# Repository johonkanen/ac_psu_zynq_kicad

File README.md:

# zynq_soc_board

Linux-capable control card for the AC in/out lab power supply, based on an AMD **Zynq-7000 (XC7Z020-CLG484)**. It
has 1 GB DDR3L (2 × x16), Gigabit Ethernet (RTL8211F) and eMMC. It plugs into the power supply baseboard
([ac_psu_kicad](https://github.com/johonkanen/ac_psu_kicad)) in the place of the Ti60F225, Agilex 5
([agilex3_soc_control_card](https://github.com/johonkanen/agilex3_soc_control_card)) and Ti135
([efinix_soc_board](https://github.com/johonkanen/efinix_soc_board)) cards.

The SoC, the DDR3 and their routing are not laid out here. They are reused, as a routed block, from the open-source
[juliancoy/zynqPCB](https://github.com/juliancoy/zynqPCB) (MIT); see **[PLAN.md](PLAN.md)** and `NOTICE`. Licence: MIT.

| | |
|---|---|
| [STATUS.md](STATUS.md) | **start here:** status, decisions, next steps, how to run the tools |
| [PLAN.md](PLAN.md) | plan, source survey and decisions |
| [DDR3_REVIEW.md](DDR3_REVIEW.md) | UG933 review of the candidate DDR3 blocks |
| [POWER_BUDGET.md](POWER_BUDGET.md) | rail currents (Vivado `report_power`), regulators, thermal |
| [ZYNQ_PCB_NOTES.md](ZYNQ_PCB_NOTES.md) | Zynq-7000 rules: supplies, sequencing, boot straps, MIO, configuration pins, DDR3 routing |
| `tools/ddr3_review.py` | die-to-die DDR delay and topology check (KiCad Python) |
| `tools/zsolve_cases.py` | impedance and propagation speed for the stack-up (uses `tools/zsolve.py`) |
| `tools/stackup_scan.py` | impedance of one trace width on every layer of the JLC 8-layer templates |
| [REUSE_LOG.md](REUSE_LOG.md) | every change to the reused DDR3 block |
| `vivado/pinplan/` | Vivado pin plan: `pinplan.py` builds and checks the PS7 + PL pins; results in `zynq_pinplan.csv`, `ps7_mio.csv`, `mio.csv` |

Set-up after cloning:

```
git submodule update --init   # tools/jlc (jlc-tools), tools/p2k (proteus2kicad, KiCad 10 env), reference/zynqpcb (DDR3 source)
```

KiCad 10 runs through `tools/p2k/bin/kicad_env.sh` (AppImage at `~/kicad/kicad-10.0.7-x86_64.AppImage`). Vivado 2024.2
runs the pin plan (`vivado/pinplan/pinplan.py`).

Status: phase 3, placement (schematic done, DDR3 block imported, parts placed); next: routing. See
[STATUS.md](STATUS.md).

## Board

<!-- board-plots:start -->
<!-- Generated by kicad-board-plots; edits between these markers are overwritten. -->

3D renders and copper layers of `kicad/zynq_card.kicad_pcb`, the layers in stack order without silkscreen. Plotted by [kicad-board-plots](https://github.com/johonkanen/kicad-board-plots) on each board change; the images live on the `renders` branch.

<table>
<tr>
<td align="center"><br><b>3D, top</b></td>
<td align="center"><br><b>3D, bottom (seen from below)</b></td>
</tr>
<tr>
<td align="center"><br><b>F.Cu: signal, GND, 1V35 pours (top)</b></td>
<td align="center"><br><b>In1.Cu: GND plane</b></td>
</tr>
<tr>
<td align="center"><br><b>In2.Cu: signal, 1V8 pour</b></td>
<td align="center"><br><b>In3.Cu: GND plane</b></td>
</tr>
<tr>
<td align="center"><br><b>In4.Cu: signal, VCCAUX, 1V8 pours</b></td>
<td align="center"><br><b>In5.Cu: GND plane</b></td>
</tr>
<tr>
<td align="center"><br><b>In6.Cu: signal, VCCAUX, 3V3, 1V0 pours</b></td>
<td align="center"><br><b>B.Cu: signal, 1V8, 1V35, DDR3_VTT, 3V3, 5V0 and 2 more pours (bottom, seen from the top)</b></td>
</tr>
</table>

<!-- board-plots:end -->

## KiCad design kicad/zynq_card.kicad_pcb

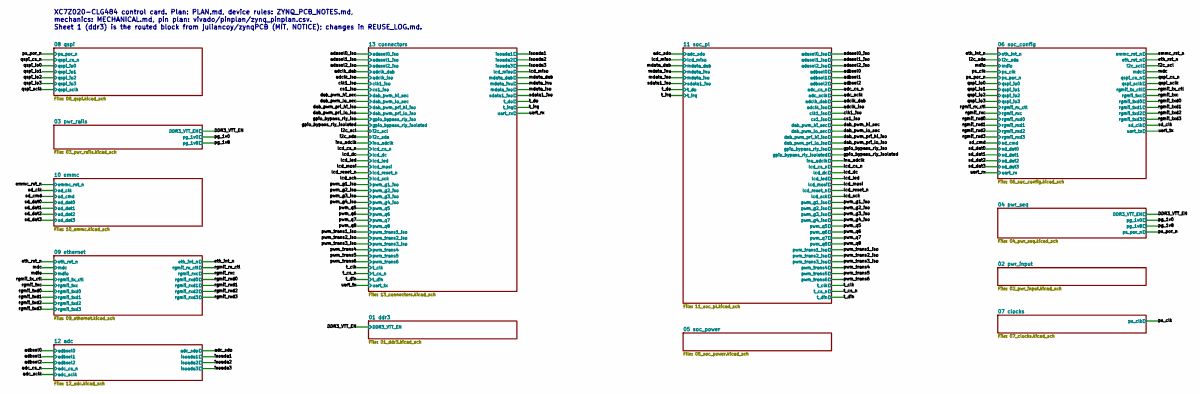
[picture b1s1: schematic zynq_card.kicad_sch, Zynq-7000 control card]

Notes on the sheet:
XC7Z020-CLG484 control card. Plan: PLAN.md, device rules: ZYNQ_PCB_NOTES.md, mechanics: MECHANICAL.md, pin plan: vivado/pinplan/zynq_pinplan.csv. Sheet 1 (ddr3) is the routed block from juliancoy/zynqPCB (MIT, NOTICE); changes in REUSE_LOG.md.

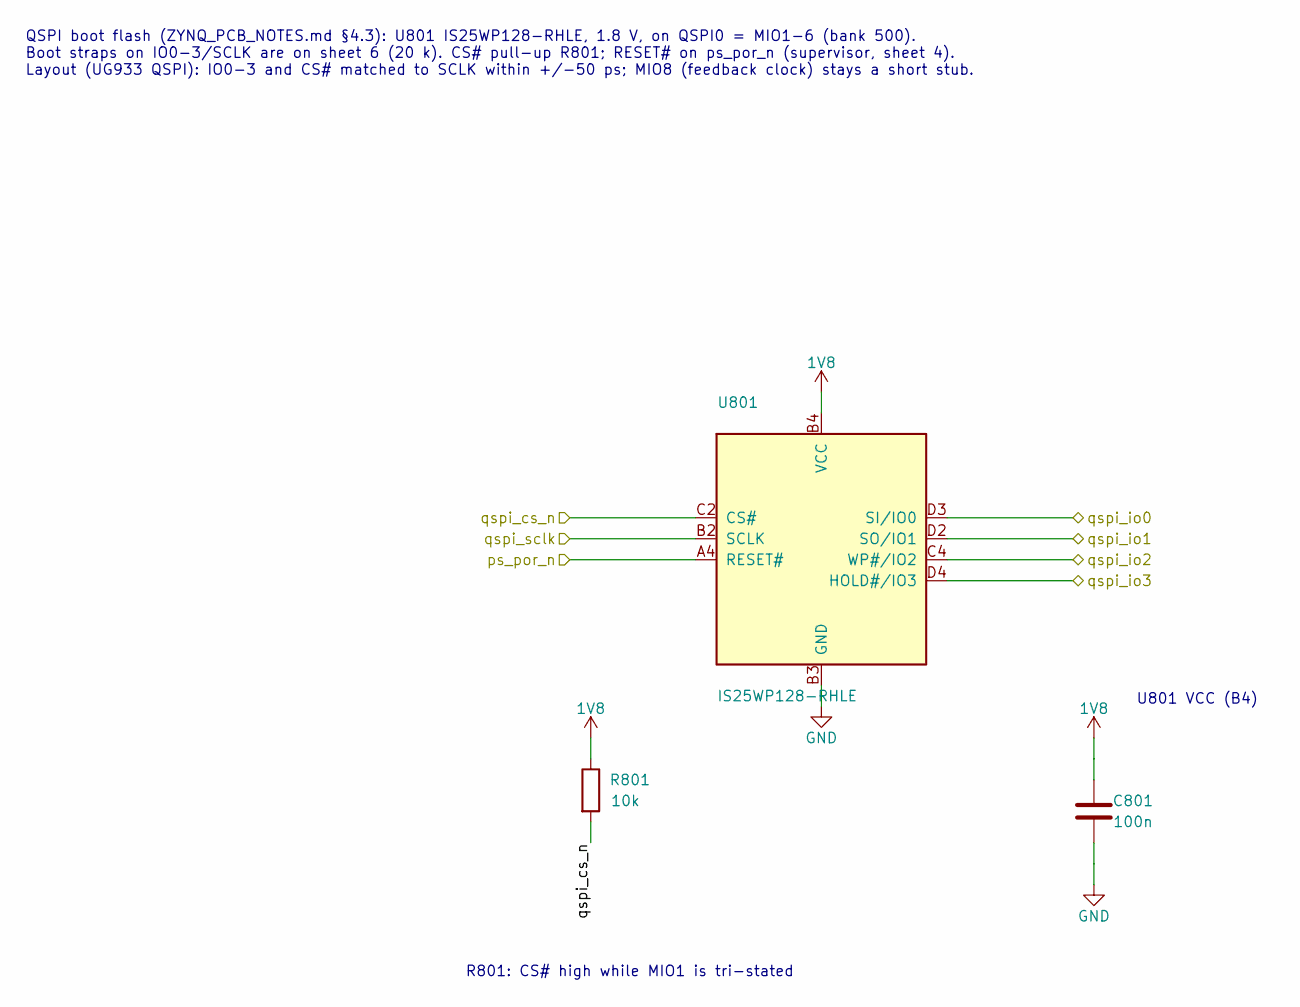
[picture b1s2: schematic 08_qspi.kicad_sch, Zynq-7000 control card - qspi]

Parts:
C801: 100n; C_0402_1005Metric; LCSC C1525
R801: 10k; R_0402_1005Metric; LCSC C25744
U801: IS25WP128-RHLE; MX25U25645G_CSP24_6x8mm_P1.0mm; LCSC C1349419

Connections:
1V8: C801.1, R801.1, U801.B4 (VCC); also elsewhere on the board
/ps_por_n: U801.A4 (RESET#); also elsewhere on the board
/qspi_cs_n: R801.2, U801.C2 (CS#); also elsewhere on the board
/qspi_io0: U801.D3 (SI/IO0); also elsewhere on the board
/qspi_io1: U801.D2 (SO/IO1); also elsewhere on the board
/qspi_io2: U801.C4 (WP#/IO2); also elsewhere on the board
/qspi_io3: U801.D4 (HOLD#/IO3); also elsewhere on the board
/qspi_sclk: U801.B2 (SCLK); also elsewhere on the board
GND: C801.2, U801.B3 (GND); also elsewhere on the board

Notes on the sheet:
QSPI boot flash (ZYNQ_PCB_NOTES.md §4.3): U801 IS25WP128-RHLE, 1.8 V, on QSPI0 = MIO1-6 (bank 500). Boot straps on IO0-3/SCLK are on sheet 6 (20 k). CS# pull-up R801; RESET# on ps_por_n (supervisor, sheet 4). Layout (UG933 QSPI): IO0-3 and CS# matched to SCLK within +/-50 ps; MIO8 (feedback clock) 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
R801: CS# high while MIO1 is tri-stated
U801 VCC (B4)

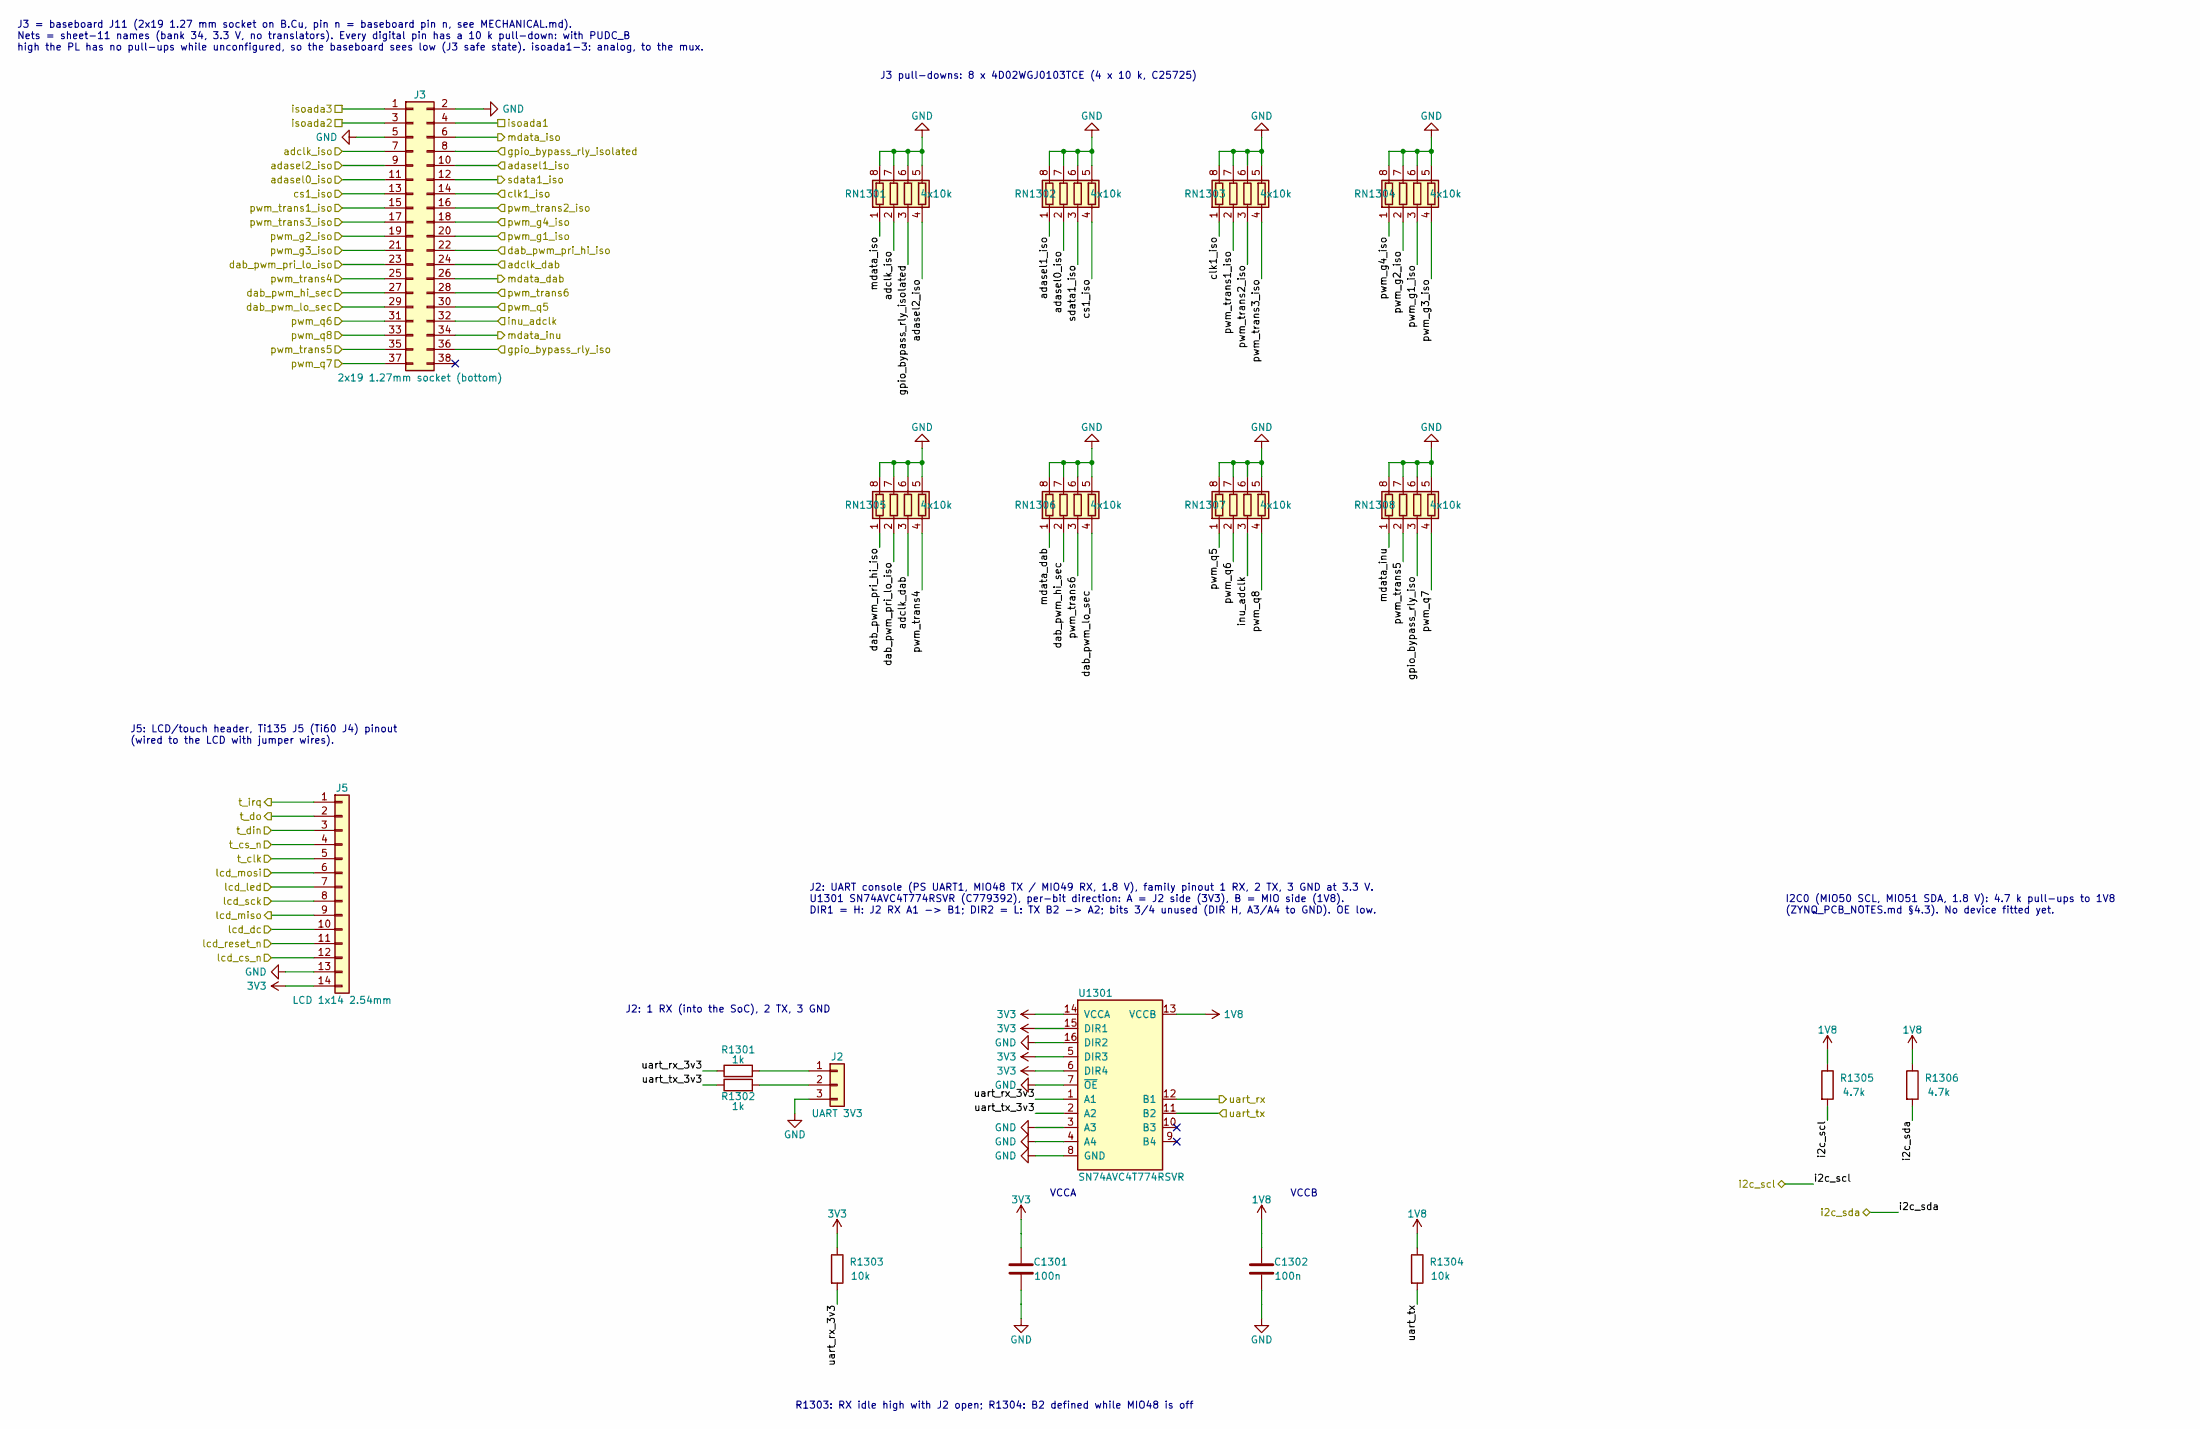
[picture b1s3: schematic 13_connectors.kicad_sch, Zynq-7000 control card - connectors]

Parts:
C1301, C1302: 100n; C_0402_1005Metric; LCSC C1525
J2: UART 3V3; PinHeader_1x03_P2.54mm_Vertical
J3: 2x19 1.27mm socket (bottom); PinSocket_2x19_P1.27mm_Vertical
J5: LCD 1x14 2.54mm; PinHeader_1x14_P2.54mm_Vertical
R1301, R1302: 1k; R_0402_1005Metric; LCSC C11702
R1303, R1304: 10k; R_0402_1005Metric; LCSC C25744
R1305, R1306: 4.7k; R_0402_1005Metric; LCSC C25900
RN1301, RN1302, RN1303, RN1304, RN1305, RN1306, RN1307, RN1308: 4x10k; R_Array_Convex_4x0402; MPN 4D02WGJ0103TCE; LCSC C25725
U1301: SN74AVC4T774RSVR; UQFN-16_1.8x2.6mm_P0.4mm; MPN SN74AVC4T774RSVR; LCSC C779392

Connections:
1V8: C1302.1, R1304.1, R1305.1, R1306.1, U1301.13 (VCCB); also elsewhere on the board
3V3: C1301.1, J5.14, R1303.1, U1301.5 (DIR3), U1301.6 (DIR4), U1301.14 (VCCA), U1301.15 (DIR1); also elsewhere on the board
/13 connectors/uart_rx_3v3: R1301.1, R1303.2, U1301.1 (A1)
/13 connectors/uart_tx_3v3: R1302.1, U1301.2 (A2)
/adasel0_iso: J3.11, RN1302.2 (R2.1); also elsewhere on the board
/adasel1_iso: J3.10, RN1302.1 (R1.1); also elsewhere on the board
/adasel2_iso: J3.9, RN1301.4 (R4.1); also elsewhere on the board
/adclk_dab: J3.24, RN1305.3 (R3.1); also elsewhere on the board
/adclk_iso: J3.7, RN1301.2 (R2.1); also elsewhere on the board
/clk1_iso: J3.14, RN1303.1 (R1.1); also elsewhere on the board
/cs1_iso: J3.13, RN1302.4 (R4.1); also elsewhere on the board
/dab_pwm_hi_sec: J3.27, RN1306.2 (R2.1); also elsewhere on the board
/dab_pwm_lo_sec: J3.29, RN1306.4 (R4.1); also elsewhere on the board
/dab_pwm_pri_hi_iso: J3.22, RN1305.1 (R1.1); also elsewhere on the board
/dab_pwm_pri_lo_iso: J3.23, RN1305.2 (R2.1); also elsewhere on the board
/gpio_bypass_rly_iso: J3.36, RN1308.3 (R3.1); also elsewhere on the board
/gpio_bypass_rly_isolated: J3.8, RN1301.3 (R3.1); also elsewhere on the board
/i2c_scl: R1305.2; also elsewhere on the board
/i2c_sda: R1306.2; also elsewhere on the board
/inu_adclk: J3.32, RN1307.3 (R3.1); also elsewhere on the board
/isoada1: J3.4; also elsewhere on the board
/isoada2: J3.3; also elsewhere on the board
/isoada3: J3.1; also elsewhere on the board
/lcd_cs_n: J5.12; also elsewhere on the board
/lcd_dc: J5.10; also elsewhere on the board
/lcd_led: J5.7; also elsewhere on the board
/lcd_miso: J5.9; also elsewhere on the board
/lcd_mosi: J5.6; also elsewhere on the board
/lcd_reset_n: J5.11; also elsewhere on the board
/lcd_sck: J5.8; also elsewhere on the board
/mdata_dab: J3.26, RN1306.1 (R1.1); also elsewhere on the board
/mdata_inu: J3.34, RN1308.1 (R1.1); also elsewhere on the board
/mdata_iso: J3.6, RN1301.1 (R1.1); also elsewhere on the board
/pwm_g1_iso: J3.20, RN1304.3 (R3.1); also elsewhere on the board
/pwm_g2_iso: J3.19, RN1304.2 (R2.1); also elsewhere on the board
/pwm_g3_iso: J3.21, RN1304.4 (R4.1); also elsewhere on the board
/pwm_g4_iso: J3.18, RN1304.1 (R1.1); also elsewhere on the board
/pwm_q5: J3.30, RN1307.1 (R1.1); also elsewhere on the board
/pwm_q6: J3.31, RN1307.2 (R2.1); also elsewhere on the board
/pwm_q7: J3.37, RN1308.4 (R4.1); also elsewhere on the board
/pwm_q8: J3.33, RN1307.4 (R4.1); also elsewhere on the board
/pwm_trans1_iso: J3.15, RN1303.2 (R2.1); also elsewhere on the board
/pwm_trans2_iso: J3.16, RN1303.3 (R3.1); also elsewhere on the board
/pwm_trans3_iso: J3.17, RN1303.4 (R4.1); also elsewhere on the board
/pwm_trans4: J3.25, RN1305.4 (R4.1); also elsewhere on the board
/pwm_trans5: J3.35, RN1308.2 (R2.1); also elsewhere on the board
/pwm_trans6: J3.28, RN1306.3 (R3.1); also elsewhere on the board
/sdata1_iso: J3.12, RN1302.3 (R3.1); also elsewhere on the board
/t_clk: J5.5; also elsewhere on the board
/t_cs_n: J5.4; also elsewhere on the board
/t_din: J5.3; also elsewhere on the board
/t_do: J5.2; also elsewhere on the board
/t_irq: J5.1; also elsewhere on the board
/uart_rx: U1301.12 (B1); also elsewhere on the board
/uart_tx: R1304.2, U1301.11 (B2); also elsewhere on the board
GND: C1301.2, C1302.2, J2.3, J3.2, J3.5, J5.13, RN1301.5 (R4.2), RN1301.6 (R3.2), RN1301.7 (R2.2), RN1301.8 (R1.2), RN1302.5 (R4.2), RN1302.6 (R3.2), RN1302.7 (R2.2), RN1302.8 (R1.2), RN1303.5 (R4.2), RN1303.6 (R3.2), RN1303.7 (R2.2), RN1303.8 (R1.2), RN1304.5 (R4.2), RN1304.6 (R3.2), RN1304.7 (R2.2), RN1304.8 (R1.2), RN1305.5 (R4.2), RN1305.6 (R3.2), RN1305.7 (R2.2), RN1305.8 (R1.2), RN1306.5 (R4.2), RN1306.6 (R3.2), RN1306.7 (R2.2), RN1306.8 (R1.2), RN1307.5 (R4.2), RN1307.6 (R3.2), RN1307.7 (R2.2), RN1307.8 (R1.2), RN1308.5 (R4.2), RN1308.6 (R3.2), RN1308.7 (R2.2), RN1308.8 (R1.2), U1301.3 (A3), U1301.4 (A4), U1301.7 (~OE), U1301.8 (GND), U1301.16 (DIR2); also elsewhere on the board
unnamed: J2.1, R1301.2
unnamed: J2.2, R1302.2

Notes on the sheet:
J3 = baseboard J11 (2x19 1.27 mm socket on B.Cu, pin n = baseboard pin n, see MECHANICAL.md). Nets = sheet-11 names (bank 34, 3.3 V, no translators). Every digital pin has a 10 k pull-down: with PUDC_B high the PL has no pull-ups while unconfigured, so the baseboard sees low (J3 safe state). isoada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
J3 pull-downs: 8 x 4D02WGJ0103TCE (4 x 10 k, C25725)
J5: LCD/touch header, Ti135 J5 (Ti60 J4) pinout (wired to the LCD with jumper wires).
J2: UART console (PS UART1, MIO48 TX / MIO49 RX, 1.8 V), family pinout 1 RX, 2 TX, 3 GND at 3.3 V. U1301 SN74AVC4T774RSVR (C779392), per-bit direction: A = J2 side (3V3), B = MIO side (1V8). DIR1 = H: J2 RX A1 -> B1; DIR2 = L: TX B2 -> A2; bits 3/4 unused (DIR H, A3/A4 to GND). OE low.
VCCA
VCCB
J2: 1 RX (into the SoC), 2 TX, 3 GND
R1303: RX idle high with J2 open; R1304: B2 defined while MIO48 is off
I2C0 (MIO50 SCL, MIO51 SDA, 1.8 V): 4.7 k pull-ups to 1V8 (ZYNQ_PCB_NOTES.md §4.3). No device fitted yet.

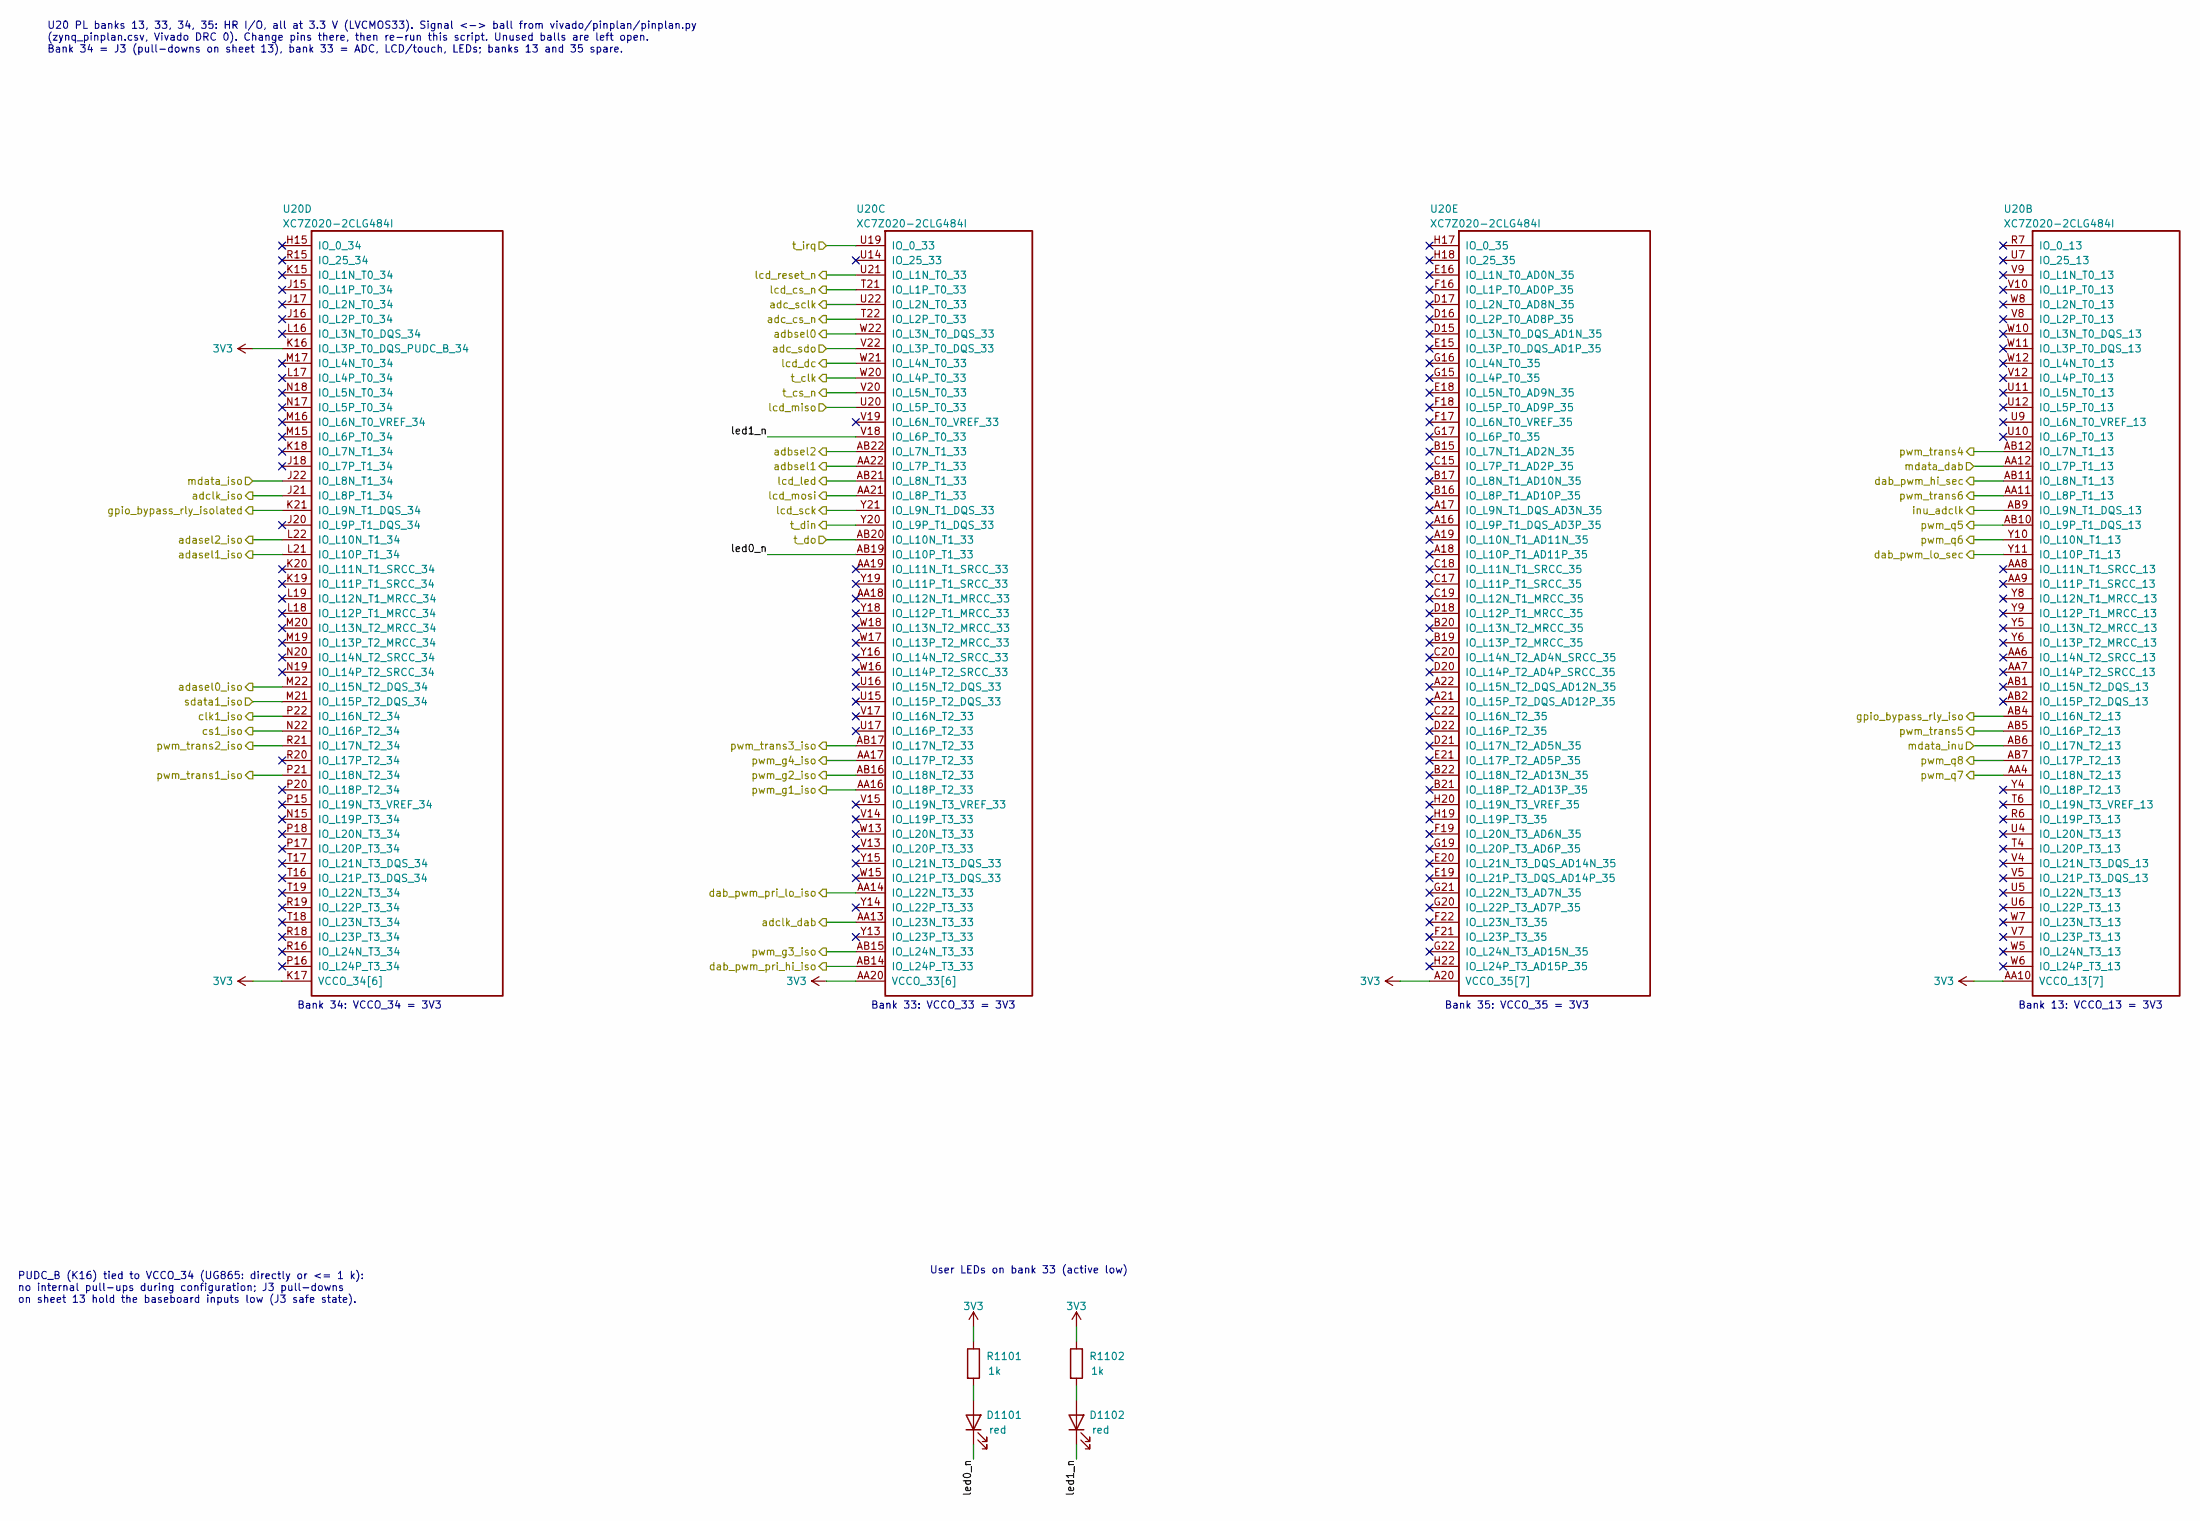
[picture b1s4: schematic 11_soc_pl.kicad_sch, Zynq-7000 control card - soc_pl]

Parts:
D1101, D1102: red; LED_0603_1608Metric; MPN KT-0603R; LCSC C2286
R1101, R1102: 1k; R_0402_1005Metric; LCSC C11702
U20: XC7Z020-2CLG484I; BGA-484_19.0x19.0mm_Layout22x22_P0.80mm_dia0.40mm; MPN XC7Z020-2CLG484I; LCSC C157624

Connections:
3V3: R1101.1, R1102.1, U20.A20 (VCCO_35[7]), U20.AA10 (VCCO_13[7]), U20.AA20 (VCCO_33[6]), U20.AB3 (VCCO_13[7]), U20.AB13 (VCCO_33[6]), U20.C16 (VCCO_35[7]), U20.D19 (VCCO_35[7]), U20.E22 (VCCO_35[7]), U20.F15 (VCCO_35[7]), U20.G18 (VCCO_35[7]), U20.H21 (VCCO_35[7]), U20.K16 (IO_L3P_T0_DQS_PUDC_B_34), U20.K17 (VCCO_34[6]), U20.L20 (VCCO_34[6]), U20.N16 (VCCO_34[6]), U20.P19 (VCCO_34[6]), U20.R22 (VCCO_34[6]), U20.T5 (VCCO_13[7]), U20.T15 (VCCO_34[6]), U20.U8 (VCCO_13[7]), U20.U18 (VCCO_33[6]), U20.V11 (VCCO_13[7]), U20.V21 (VCCO_33[6]), U20.W4 (VCCO_13[7]), U20.W14 (VCCO_33[6]), U20.Y7 (VCCO_13[7]), U20.Y17 (VCCO_33[6]); also elsewhere on the board
/11 soc_pl/led0_n: D1101.1 (K), U20.AB19 (IO_L10P_T1_33)
/11 soc_pl/led1_n: D1102.1 (K), U20.V18 (IO_L6P_T0_33)
/adasel0_iso: U20.M22 (IO_L15N_T2_DQS_34); also elsewhere on the board
/adasel1_iso: U20.L21 (IO_L10P_T1_34); also elsewhere on the board
/adasel2_iso: U20.L22 (IO_L10N_T1_34); also elsewhere on the board
/adbsel0: U20.W22 (IO_L3N_T0_DQS_33); also elsewhere on the board
/adbsel1: U20.AA22 (IO_L7P_T1_33); also elsewhere on the board
/adbsel2: U20.AB22 (IO_L7N_T1_33); also elsewhere on the board
/adc_cs_n: U20.T22 (IO_L2P_T0_33); also elsewhere on the board
/adc_sclk: U20.U22 (IO_L2N_T0_33); also elsewhere on the board
/adc_sdo: U20.V22 (IO_L3P_T0_DQS_33); also elsewhere on the board
/adclk_dab: U20.AA13 (IO_L23N_T3_33); also elsewhere on the board
/adclk_iso: U20.J21 (IO_L8P_T1_34); also elsewhere on the board
/clk1_iso: U20.P22 (IO_L16N_T2_34); also elsewhere on the board
/cs1_iso: U20.N22 (IO_L16P_T2_34); also elsewhere on the board
/dab_pwm_hi_sec: U20.AB11 (IO_L8N_T1_13); also elsewhere on the board
/dab_pwm_lo_sec: U20.Y11 (IO_L10P_T1_13); also elsewhere on the board
/dab_pwm_pri_hi_iso: U20.AB14 (IO_L24P_T3_33); also elsewhere on the board
/dab_pwm_pri_lo_iso: U20.AA14 (IO_L22N_T3_33); also elsewhere on the board
/gpio_bypass_rly_iso: U20.AB4 (IO_L16N_T2_13); also elsewhere on the board
/gpio_bypass_rly_isolated: U20.K21 (IO_L9N_T1_DQS_34); also elsewhere on the board
/inu_adclk: U20.AB9 (IO_L9N_T1_DQS_13); also elsewhere on the board
/lcd_cs_n: U20.T21 (IO_L1P_T0_33); also elsewhere on the board
/lcd_dc: U20.W21 (IO_L4N_T0_33); also elsewhere on the board
/lcd_led: U20.AB21 (IO_L8N_T1_33); also elsewhere on the board
/lcd_miso: U20.U20 (IO_L5P_T0_33); also elsewhere on the board
/lcd_mosi: U20.AA21 (IO_L8P_T1_33); also elsewhere on the board
/lcd_reset_n: U20.U21 (IO_L1N_T0_33); also elsewhere on the board
/lcd_sck: U20.Y21 (IO_L9N_T1_DQS_33); also elsewhere on the board
/mdata_dab: U20.AA12 (IO_L7P_T1_13); also elsewhere on the board
/mdata_inu: U20.AB6 (IO_L17N_T2_13); also elsewhere on the board
/mdata_iso: U20.J22 (IO_L8N_T1_34); also elsewhere on the board
/pwm_g1_iso: U20.AA16 (IO_L18P_T2_33); also elsewhere on the board
/pwm_g2_iso: U20.AB16 (IO_L18N_T2_33); also elsewhere on the board
/pwm_g3_iso: U20.AB15 (IO_L24N_T3_33); also elsewhere on the board
/pwm_g4_iso: U20.AA17 (IO_L17P_T2_33); also elsewhere on the board
/pwm_q5: U20.AB10 (IO_L9P_T1_DQS_13); also elsewhere on the board
/pwm_q6: U20.Y10 (IO_L10N_T1_13); also elsewhere on the board
/pwm_q7: U20.AA4 (IO_L18N_T2_13); also elsewhere on the board
/pwm_q8: U20.AB7 (IO_L17P_T2_13); also elsewhere on the board
/pwm_trans1_iso: U20.P21 (IO_L18N_T2_34); also elsewhere on the board
/pwm_trans2_iso: U20.R21 (IO_L17N_T2_34); also elsewhere on the board
/pwm_trans3_iso: U20.AB17 (IO_L17N_T2_33); also elsewhere on the board
/pwm_trans4: U20.AB12 (IO_L7N_T1_13); also elsewhere on the board
/pwm_trans5: U20.AB5 (IO_L16P_T2_13); also elsewhere on the board
/pwm_trans6: U20.AA11 (IO_L8P_T1_13); also elsewhere on the board
/sdata1_iso: U20.M21 (IO_L15P_T2_DQS_34); also elsewhere on the board
/t_clk: U20.W20 (IO_L4P_T0_33); also elsewhere on the board
/t_cs_n: U20.V20 (IO_L5N_T0_33); also elsewhere on the board
/t_din: U20.Y20 (IO_L9P_T1_DQS_33); also elsewhere on the board
/t_do: U20.AB20 (IO_L10N_T1_33); also elsewhere on the board
/t_irq: U20.U19 (IO_0_33); also elsewhere on the board
unnamed: D1101.2 (A), R1101.2
unnamed: D1102.2 (A), R1102.2

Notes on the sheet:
U20 PL banks 13, 33, 34, 35: HR I/O, all at 3.3 V (LVCMOS33). Signal <-> ball from vivado/pinplan/pinplan.py (zynq_pinplan.csv, Vivado DRC 0). Change pins there, then re-run this script. Unused balls are left open. Bank 34 = J3 (pull-downs on sheet 13), bank 33 = ADC, LCD/touch, LEDs; banks 13 and 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
Bank 34: VCCO_34 = 3V3
Bank 33: VCCO_33 = 3V3
Bank 35: VCCO_35 = 3V3
Bank 13: VCCO_13 = 3V3
PUDC_B (K16) tied to VCCO_34 (UG865: directly or <= 1 k): no internal pull-ups during configuration; J3 pull-downs on sheet 13 hold the baseboard inputs low (J3 safe state).
User LEDs on bank 33 (active low)

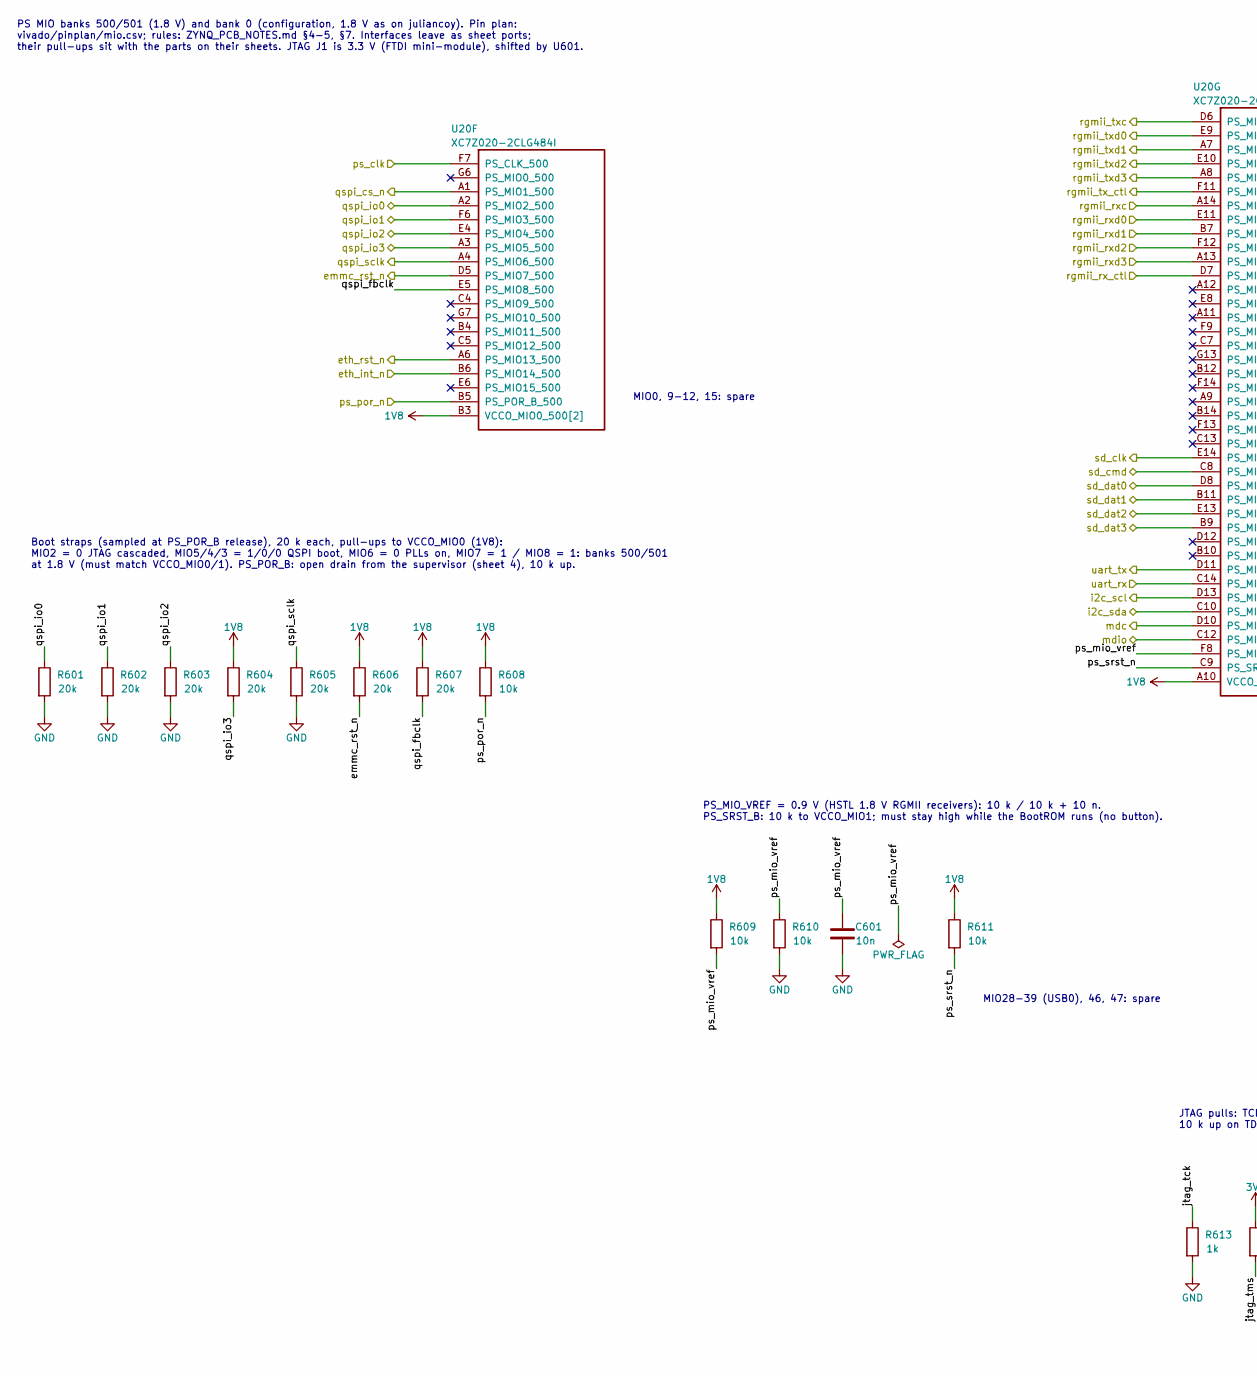
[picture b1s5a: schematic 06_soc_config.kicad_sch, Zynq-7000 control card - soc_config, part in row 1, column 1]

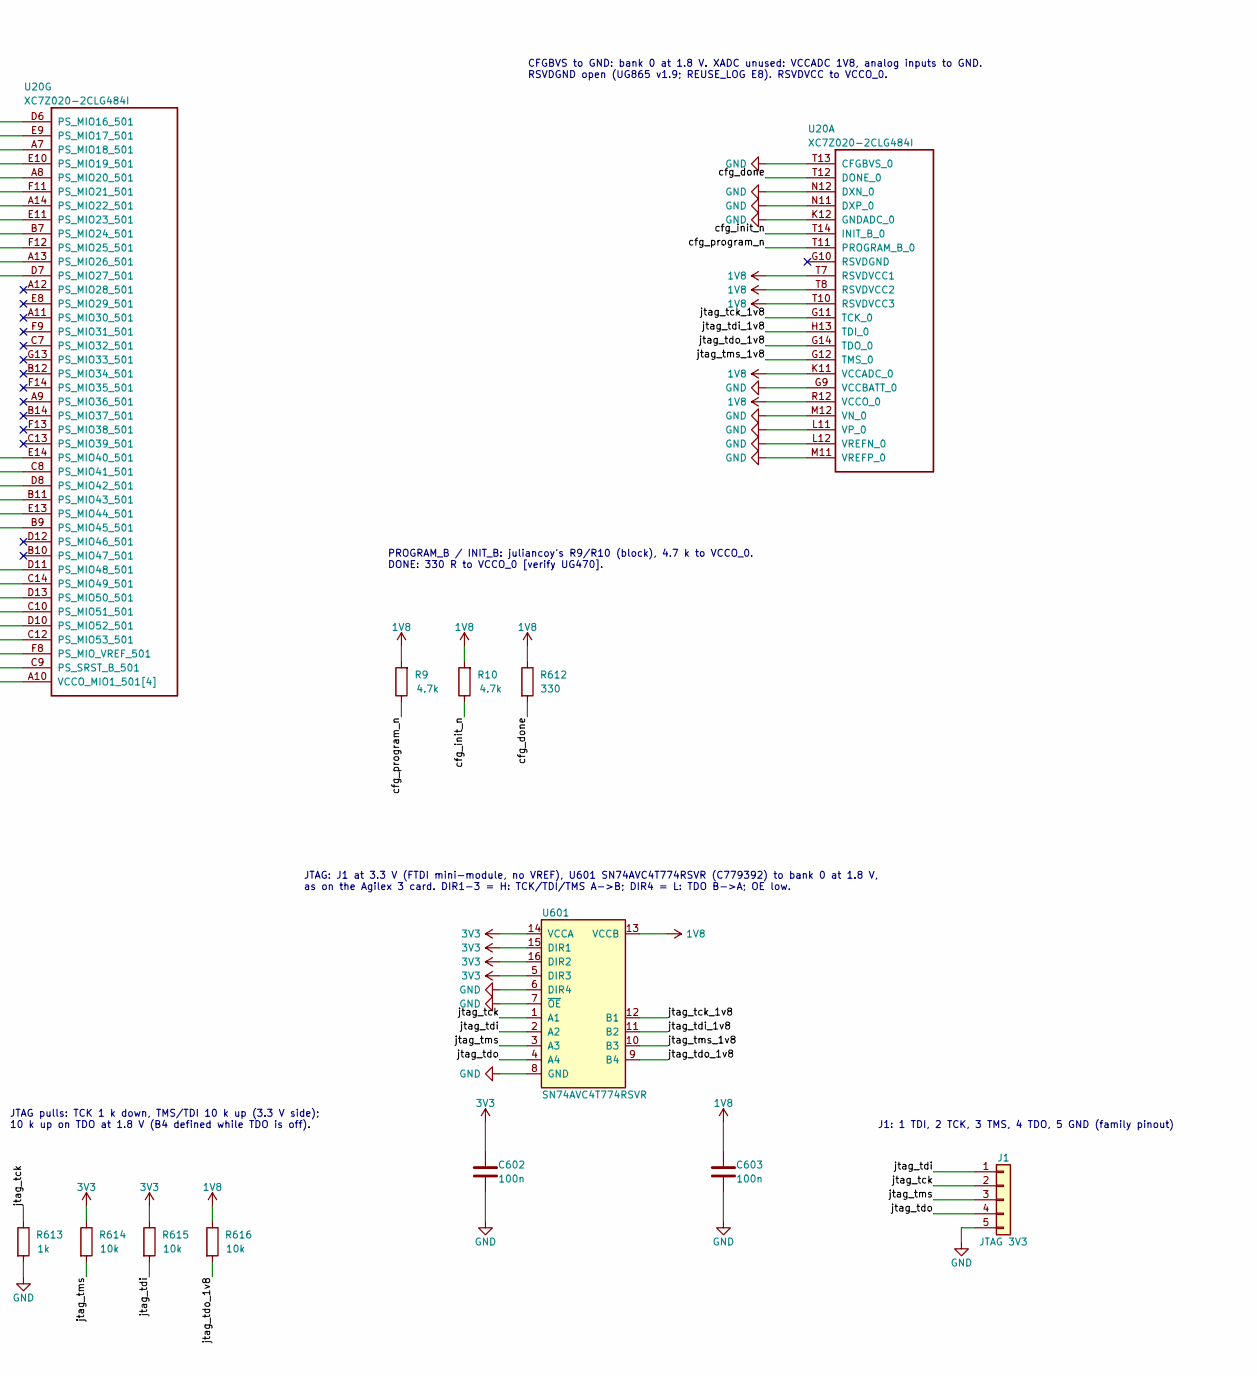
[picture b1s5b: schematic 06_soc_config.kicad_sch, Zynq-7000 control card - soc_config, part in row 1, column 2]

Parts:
C601: 10n; C_0402_1005Metric; LCSC C15195
C602, C603: 100n; C_0402_1005Metric; LCSC C1525
J1: JTAG 3V3; PinHeader_1x05_P2.54mm_Vertical
R9, R10: 4.7k; R_0402_1005Metric; LCSC C25900
R601, R602, R603, R604, R605, R606, R607: 20k; R_0402_1005Metric; LCSC C25765
R608, R609, R610, R611, R614, R615, R616: 10k; R_0402_1005Metric; LCSC C25744
R612: 330; R_0402_1005Metric; LCSC C25104
R613: 1k; R_0402_1005Metric; LCSC C11702
U20: XC7Z020-2CLG484I
U601: SN74AVC4T774RSVR; UQFN-16_1.8x2.6mm_P0.4mm; MPN SN74AVC4T774RSVR; LCSC C779392

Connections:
1V8: C603.1, R9.2, R10.2, R604.1, R606.1, R607.1, R608.1, R609.1, R611.1, R612.1, R616.1, U20.A10 (VCCO_MIO1_501[4]), U20.B3 (VCCO_MIO0_500[2]), U20.B13 (VCCO_MIO1_501[4]), U20.C6 (VCCO_MIO0_500[2]), U20.D9 (VCCO_MIO1_501[4]), U20.E12 (VCCO_MIO1_501[4]), U20.K11 (VCCADC_0), U20.R12 (VCCO_0), U20.T7 (RSVDVCC1), U20.T8 (RSVDVCC2), U20.T10 (RSVDVCC3), U601.13 (VCCB); also elsewhere on the board
3V3: C602.1, R614.1, R615.1, U601.5 (DIR3), U601.14 (VCCA), U601.15 (DIR1), U601.16 (DIR2); also elsewhere on the board
/06 soc_config/cfg_done: R612.2, U20.T12 (DONE_0)
/06 soc_config/cfg_init_n: R10.1, U20.T14 (INIT_B_0)
/06 soc_config/cfg_program_n: R9.1, U20.T11 (PROGRAM_B_0)
/06 soc_config/jtag_tck: J1.2, R613.1, U601.1 (A1)
/06 soc_config/jtag_tck_1v8: U20.G11 (TCK_0), U601.12 (B1)
/06 soc_config/jtag_tdi: J1.1, R615.2, U601.2 (A2)
/06 soc_config/jtag_tdi_1v8: U20.H13 (TDI_0), U601.11 (B2)
/06 soc_config/jtag_tdo: J1.4, U601.4 (A4)
/06 soc_config/jtag_tdo_1v8: R616.2, U20.G14 (TDO_0), U601.9 (B4)
/06 soc_config/jtag_tms: J1.3, R614.2, U601.3 (A3)
/06 soc_config/jtag_tms_1v8: U20.G12 (TMS_0), U601.10 (B3)
/06 soc_config/ps_mio_vref: C601.1, R609.2, R610.1, U20.F8 (PS_MIO_VREF_501)
/06 soc_config/ps_srst_n: R611.2, U20.C9 (PS_SRST_B_501)
/06 soc_config/qspi_fbclk: R607.2, U20.E5 (PS_MIO8_500)
/emmc_rst_n: R606.2, U20.D5 (PS_MIO7_500); also elsewhere on the board
/eth_int_n: U20.B6 (PS_MIO14_500); also elsewhere on the board
/eth_rst_n: U20.A6 (PS_MIO13_500); also elsewhere on the board
/i2c_scl: U20.D13 (PS_MIO50_501); also elsewhere on the board
/i2c_sda: U20.C10 (PS_MIO51_501); also elsewhere on the board
/mdc: U20.D10 (PS_MIO52_501); also elsewhere on the board
/mdio: U20.C12 (PS_MIO53_501); also elsewhere on the board
/ps_clk: U20.F7 (PS_CLK_500); also elsewhere on the board
/ps_por_n: R608.2, U20.B5 (PS_POR_B_500); also elsewhere on the board
/qspi_cs_n: U20.A1 (PS_MIO1_500); also elsewhere on the board
/qspi_io0: R601.1, U20.A2 (PS_MIO2_500); also elsewhere on the board
/qspi_io1: R602.1, U20.F6 (PS_MIO3_500); also elsewhere on the board
/qspi_io2: R603.1, U20.E4 (PS_MIO4_500); also elsewhere on the board
/qspi_io3: R604.2, U20.A3 (PS_MIO5_500); also elsewhere on the board
/qspi_sclk: R605.1, U20.A4 (PS_MIO6_500); also elsewhere on the board
/rgmii_rx_ctl: U20.D7 (PS_MIO27_501); also elsewhere on the board
/rgmii_rxc: U20.A14 (PS_MIO22_501); also elsewhere on the board
/rgmii_rxd0: U20.E11 (PS_MIO23_501); also elsewhere on the board
/rgmii_rxd1: U20.B7 (PS_MIO24_501); also elsewhere on the board
/rgmii_rxd2: U20.F12 (PS_MIO25_501); also elsewhere on the board
/rgmii_rxd3: U20.A13 (PS_MIO26_501); also elsewhere on the board
/rgmii_tx_ctl: U20.F11 (PS_MIO21_501); also elsewhere on the board
/rgmii_txc: U20.D6 (PS_MIO16_501); also elsewhere on the board
/rgmii_txd0: U20.E9 (PS_MIO17_501); also elsewhere on the board
/rgmii_txd1: U20.A7 (PS_MIO18_501); also elsewhere on the board
/rgmii_txd2: U20.E10 (PS_MIO19_501); also elsewhere on the board
/rgmii_txd3: U20.A8 (PS_MIO20_501); also elsewhere on the board
/sd_clk: U20.E14 (PS_MIO40_501); also elsewhere on the board
/sd_cmd: U20.C8 (PS_MIO41_501); also elsewhere on the board
/sd_dat0: U20.D8 (PS_MIO42_501); also elsewhere on the board
/sd_dat1: U20.B11 (PS_MIO43_501); also elsewhere on the board
/sd_dat2: U20.E13 (PS_MIO44_501); also elsewhere on the board
/sd_dat3: U20.B9 (PS_MIO45_501); also elsewhere on the board
/uart_rx: U20.C14 (PS_MIO49_501); also elsewhere on the board
/uart_tx: U20.D11 (PS_MIO48_501); also elsewhere on the board
GND: C601.2, C602.2, C603.2, J1.5, R601.2, R602.2, R603.2, R605.2, R610.2, R613.2, U20.G9 (VCCBATT_0), U20.K12 (GNDADC_0), U20.L11 (VP_0), U20.L12 (VREFN_0), U20.M11 (VREFP_0), U20.M12 (VN_0), U20.N11 (DXP_0), U20.N12 (DXN_0), U20.T13 (CFGBVS_0), U601.6 (DIR4), U601.7 (~OE), U601.8 (GND); also elsewhere on the board

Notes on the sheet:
PS MIO banks 500/501 (1.8 V) and bank 0 (configuration, 1.8 V as on juliancoy). Pin plan: vivado/pinplan/mio.csv; rules: ZYNQ_PCB_NOTES.md §4-5, §7. Interfaces leave as sheet ports; their pull-ups sit with the parts on their sheets. JTAG J1 is 3.3 V (FTDI mini-module), shifted by U601.
MIO0, 9-12, 15: spare
Boot straps (sampled at PS_POR_B release), 20 k each, pull-ups to VCCO_MIO0 (1V8): MIO2 = 0 JTAG cascaded, MIO5/4/3 = 1/0/0 QSPI boot, MIO6 = 0 PLLs on, MIO7 = 1 / MIO8 = 1: banks 500/501 at 1.8 V (must match VCCO_MIO0/1). PS_POR_B: open drain from the supervisor (sheet 4), 10 k up.
MIO28-39 (USB0), 46, 47: spare
PS_MIO_VREF = 0.9 V (HSTL 1.8 V RGMII receivers): 10 k / 10 k + 10 n. PS_SRST_B: 10 k to VCCO_MIO1; must stay high while the BootROM runs (no button).
CFGBVS to GND: bank 0 at 1.8 V. XADC unused: VCCADC 1V8, analog inputs to GND. RSVDGND open (UG865 v1.9; REUSE_LOG E8). RSVDVCC to VCCO_0.
PROGRAM_B / INIT_B: juliancoy's R9/R10 (block), 4.7 k to VCCO_0. DONE: 330 R to VCCO_0 [verify UG470].
JTAG: J1 at 3.3 V (FTDI mini-module, no VREF), U601 SN74AVC4T774RSVR (C779392) to bank 0 at 1.8 V, as on the Agilex 3 card. DIR1-3 = H: TCK/TDI/TMS A->B; DIR4 = L: TDO B->A; OE low.
JTAG pulls: TCK 1 k down, TMS/TDI 10 k up (3.3 V side); 10 k up on TDO at 1.8 V (B4 defined while TDO is off).
J1: 1 TDI, 2 TCK, 3 TMS, 4 TDO, 5 GND (family pinout)
